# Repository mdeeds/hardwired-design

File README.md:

# Hardwired Design

This repository contains a curated collection of "vintage" electronic
schematics recreated in KiCad format, alongside original hardware designs
for the Hardwired Design project. It serves as a resource for circuit design,
PCB layouts, and 3D models.

## Project Overview

This project is an open resource that includes reference vintage circuitry
with the designs developed for the Hardwired Design project - a public
synthesizer design and manufacturing project. All schematics and layouts
are maintained using modern EDA tools to ensure they are accessible for
contemporary manufacturing and hobbyist use.

## Setup

To get started with these designs, follow the instructions below.

### 1. Install KiCad

This project is designed for **KiCad v10.0**. Please ensure you have the
correct version installed to avoid compatibility issues with the schema and
layout files.

*   Download: [KiCad Official Website](https://www.kicad.org/download/)

### 2. Clone the Repository

Clone this repository to your local machine using Git:

```bash
git clone https://github.com/mdeeds/hardwired-design.git
```

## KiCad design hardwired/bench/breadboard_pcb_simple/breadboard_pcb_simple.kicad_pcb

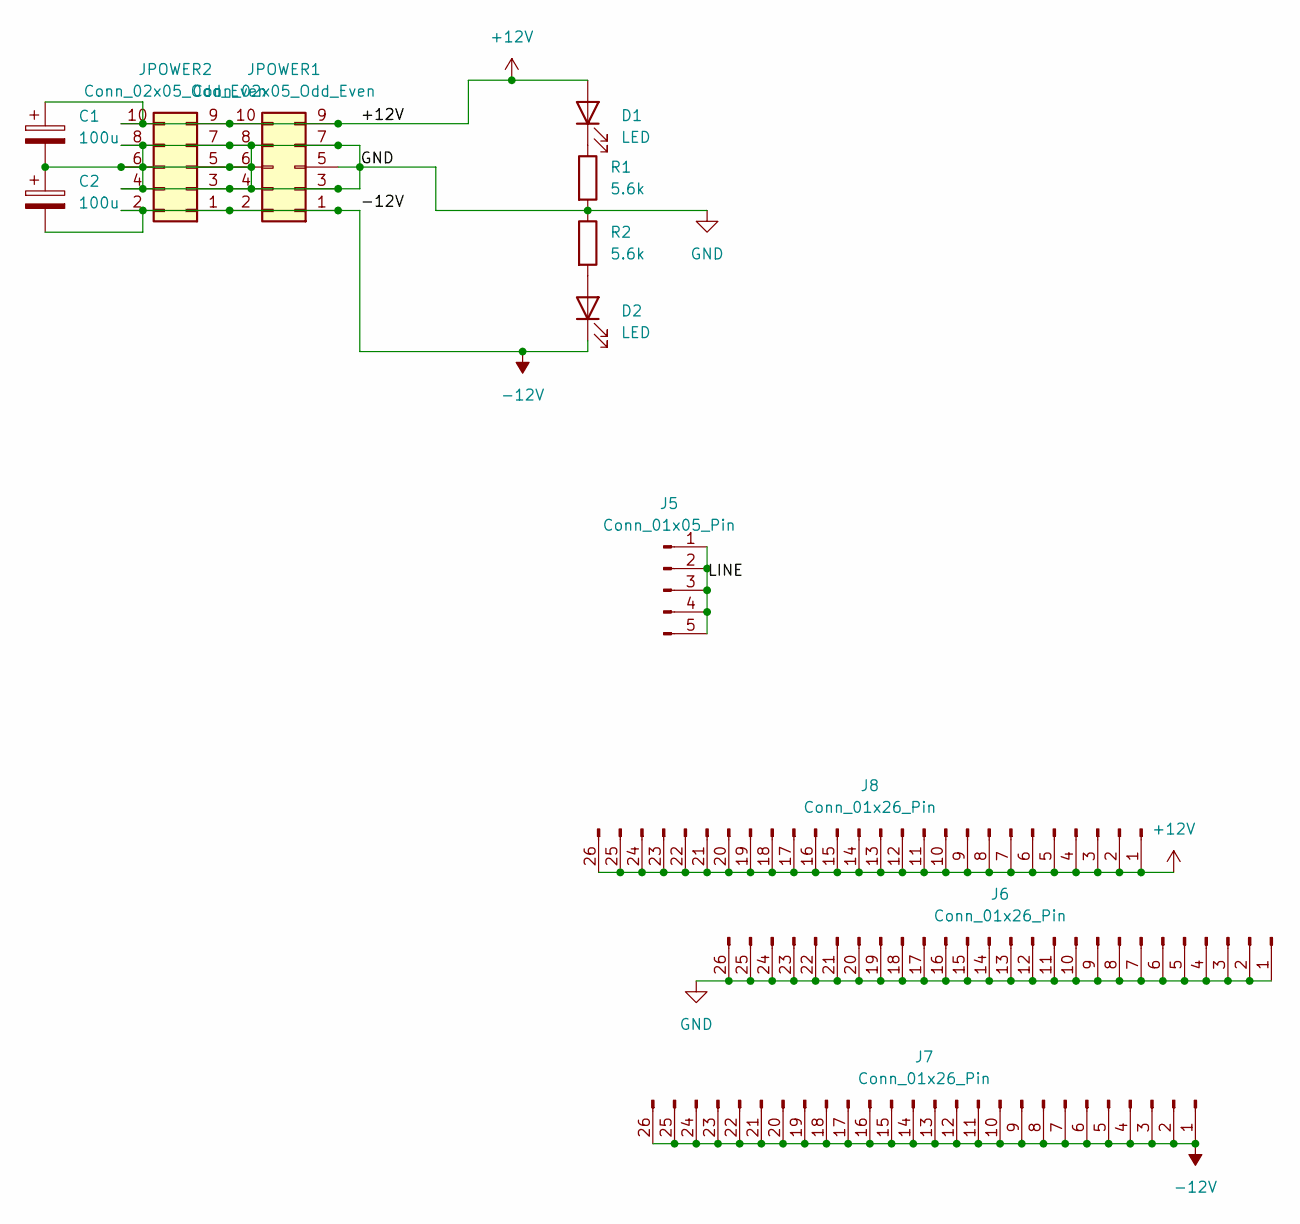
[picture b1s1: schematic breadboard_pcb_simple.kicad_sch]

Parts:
C1, C2: 100u; CP_Radial_D5.0mm_P2.00mm
D1, D2: LED; LED_D3.0mm_Clear
J5: Conn_01x05_Pin; PinHeader_1x05_P2.54mm_Vertical
J6, J7, J8: Conn_01x26_Pin; PinHeader_1x26_P2.54mm_Vertical
JPOWER1, JPOWER2: Conn_02x05_Odd_Even; Amphenol 71918-110LF 2.54 2x05 IDC
R1, R2: 5.6k; R_Axial_DIN0309_L9.0mm_D3.2mm_P2.54mm_Vertical

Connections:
+12V: C1.1, D1.2 (A), J8.1, J8.2, J8.3, J8.4, J8.5, J8.6, J8.7, J8.8, J8.9, J8.10, J8.11, J8.12, J8.13, J8.14, J8.15, J8.16, J8.17, J8.18, J8.19, J8.20, J8.21, J8.22, J8.23, J8.24, J8.25, J8.26, JPOWER1.9, JPOWER1.10, JPOWER2.9, JPOWER2.10
-12V: C2.2, D2.1 (K), J7.1, J7.2, J7.3, J7.4, J7.5, J7.6, J7.7, J7.8, J7.9, J7.10, J7.11, J7.12, J7.13, J7.14, J7.15, J7.16, J7.17, J7.18, J7.19, J7.20, J7.21, J7.22, J7.23, J7.24, J7.25, J7.26, JPOWER1.1, JPOWER1.2, JPOWER2.1, JPOWER2.2
GND: C1.2, C2.1, J6.1, J6.2, J6.3, J6.4, J6.5, J6.6, J6.7, J6.8, J6.9, J6.10, J6.11, J6.12, J6.13, J6.14, J6.15, J6.16, J6.17, J6.18, J6.19, J6.20, J6.21, J6.22, J6.23, J6.24, J6.25, J6.26, JPOWER1.3, JPOWER1.4, JPOWER1.5, JPOWER1.6, JPOWER1.7, JPOWER1.8, JPOWER2.3, JPOWER2.4, JPOWER2.5, JPOWER2.6, JPOWER2.7, JPOWER2.8, R1.2, R2.1
unnamed: D1.1 (K), R1.1
unnamed: D2.2 (A), R2.2
unnamed: J5.1, J5.2, J5.3, J5.4, J5.5

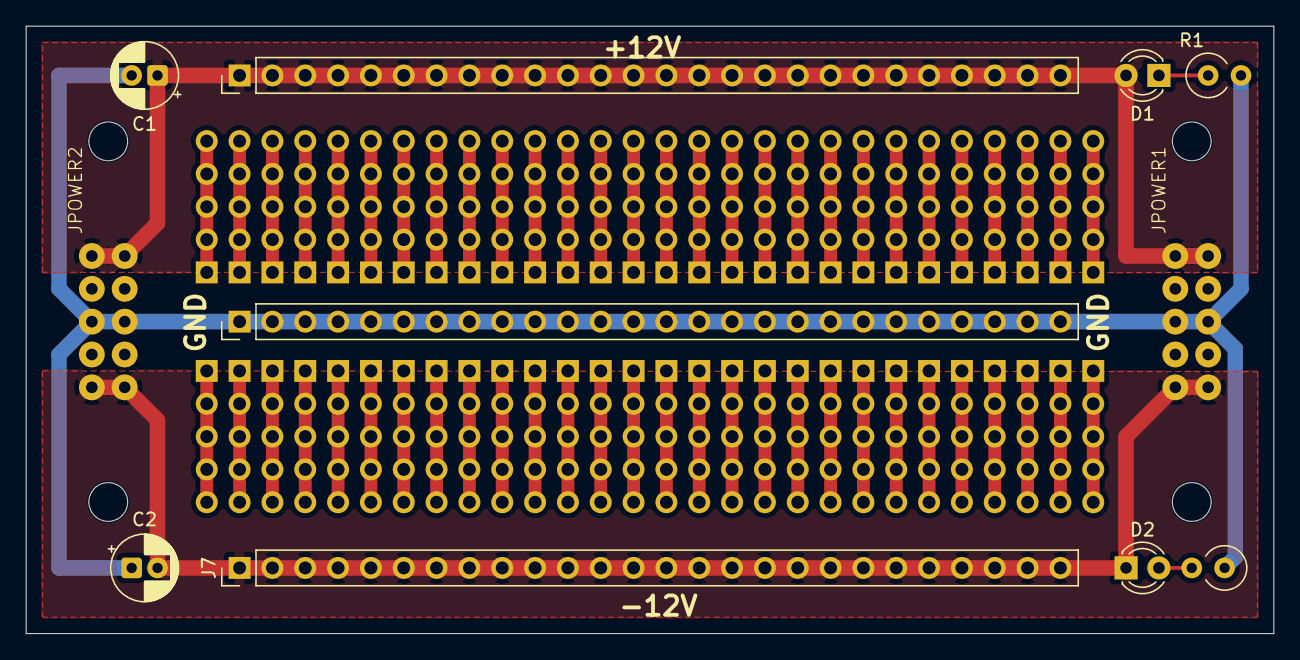
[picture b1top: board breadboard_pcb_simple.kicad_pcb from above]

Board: 2 copper layers, 96.5 x 47.0 mm, 11 parts (0 on the bottom side), 5 nets.

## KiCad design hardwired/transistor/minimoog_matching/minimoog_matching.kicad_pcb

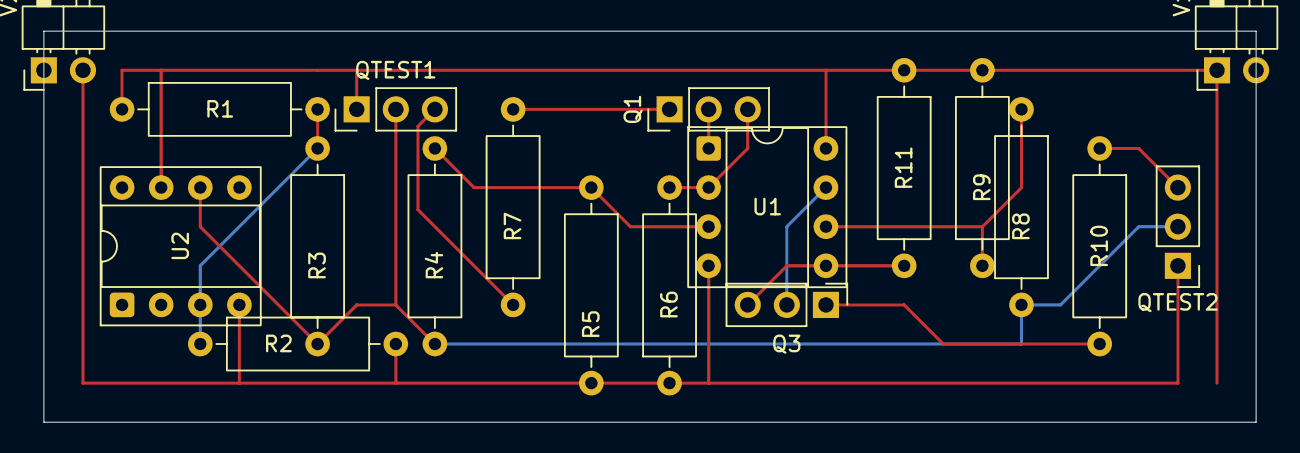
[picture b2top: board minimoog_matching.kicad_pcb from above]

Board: 2 copper layers, 78.7 x 25.4 mm, 19 parts (0 on the bottom side), 15 nets.

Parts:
Q1: NPN; PinHeader_1x03_P2.54mm_Vertical
Q3: PNP; PinHeader_1x03_P2.54mm_Vertical
QTEST1: NPN; PinHeader_1x03_P2.54mm_Vertical
QTEST2: PNP; PinHeader_1x03_P2.54mm_Vertical
R1, R2: 100k; R_Axial_DIN0309_L9.0mm_D3.2mm_P12.70mm_Horizontal
R3: 100; R_Axial_DIN0309_L9.0mm_D3.2mm_P12.70mm_Horizontal
R4, R5, R8, R9: 12k; R_Axial_DIN0309_L9.0mm_D3.2mm_P12.70mm_Horizontal
R6, R11: 47k; R_Axial_DIN0309_L9.0mm_D3.2mm_P12.70mm_Horizontal
R7, R10: 10k; R_Axial_DIN0309_L9.0mm_D3.2mm_P12.70mm_Horizontal
U1: Opamp_Dual; DIP-8_W7.62mm_Socket
U2: BUF634P; DIP-8_W7.62mm_Socket
V1, V2: 10; PinHeader_1x02_P2.54mm_Horizontal

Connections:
0: R1.2, R2.1, R3.1, U2.3 (V_{IN})
+10V: QTEST1.1 (C), R1.1, R9.2, R11.1, U1.8 (V+), U2.7 (V+), V1.1
-10V: QTEST2.1 (C), R2.2, R5.2, R6.1, U1.4 (V-), U2.4 (V-), V2.2
GND: QTEST1.2 (B), QTEST2.2 (B), R3.2, R4.2, R8.2, U2.6
unnamed: Q1.2 (B), U1.1
unnamed: Q1.1 (C), R7.2
unnamed: Q1.3 (E), R6.2, U1.2 (-)
unnamed: Q3.2 (B), U1.7
unnamed: Q3.1 (C), R10.2
unnamed: Q3.3 (E), R11.2, U1.5 (+)
unnamed: QTEST1.3 (E), R7.1
unnamed: QTEST2.3 (E), R10.1
unnamed: R4.1, R5.1, U1.3 (+)
unnamed: R8.1, R9.1, U1.6 (-)
unnamed: V1.2, V2.1

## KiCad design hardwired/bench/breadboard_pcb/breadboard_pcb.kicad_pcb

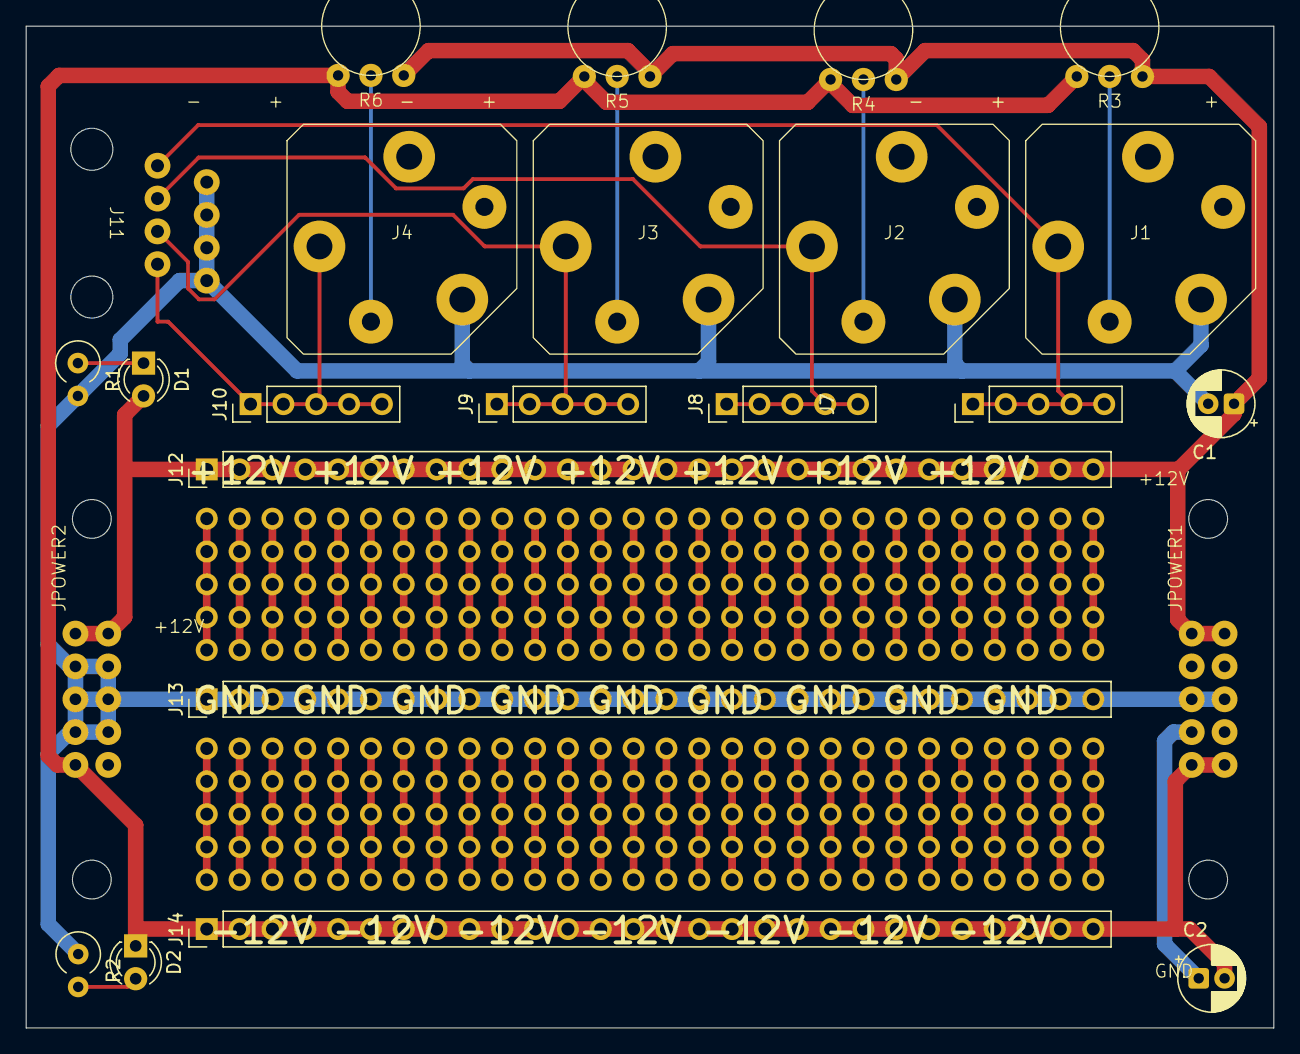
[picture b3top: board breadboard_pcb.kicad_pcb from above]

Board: 2 copper layers, 96.5 x 77.5 mm, 24 parts (0 on the bottom side), 13 nets.

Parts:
C1, C2: 100u; CP_Radial_D5.0mm_P2.00mm
D1, D2: LED; LED_D3.0mm_Clear
J1: CV1; ACJM-MV3-2S 3.5mm Audio Jack Mono Switched
J2: CV2; ACJM-MV3-2S 3.5mm Audio Jack Mono Switched
J3: CV3; ACJM-MV3-2S 3.5mm Audio Jack Mono Switched
J4: CV4; ACJM-MV3-2S 3.5mm Audio Jack Mono Switched
J7, J8, J9, J10: Conn_01x05_Pin; PinHeader_1x05_P2.54mm_Vertical
J11: RJ45; Keystone RJ45 949
J12, J13, J14: Conn_01x28_Pin; PinHeader_1x28_P2.54mm_Vertical
JPOWER1, JPOWER2: Conn_02x05_Odd_Even; Amphenol 71918-110LF 2.54 2x05 IDC
R1, R2: 330; R_Axial_DIN0309_L9.0mm_D3.2mm_P2.54mm_Vertical
R3, R4, R5, R6: Potentiometer; BOURNS 2.54 335T POTENTIOMETER

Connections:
+12V: C1.1, D1.2 (A), J12.1, J12.2, J12.3, J12.4, J12.5, J12.6, J12.7, J12.8, J12.9, J12.10, J12.11, J12.12, J12.13, J12.14, J12.15, J12.16, J12.17, J12.18, J12.19, J12.20, J12.21, J12.22, J12.23, J12.24, J12.25, J12.26, J12.27, J12.28, JPOWER1.9, JPOWER1.10, JPOWER2.9, JPOWER2.10, R3.3, R4.3, R5.3, R6.3
-12V: C2.2, D2.1 (K), J14.1, J14.2, J14.3, J14.4, J14.5, J14.6, J14.7, J14.8, J14.9, J14.10, J14.11, J14.12, J14.13, J14.14, J14.15, J14.16, J14.17, J14.18, J14.19, J14.20, J14.21, J14.22, J14.23, J14.24, J14.25, J14.26, J14.27, J14.28, JPOWER1.1, JPOWER1.2, JPOWER2.1, JPOWER2.2, R3.1, R4.1, R5.1, R6.1
/J1_T: J1.T, J7.1, J7.2, J7.3, J7.4, J7.5, J11.1
/J1_TN: J1.TN, R3.2
/J2_T: J2.T, J8.1, J8.2, J8.3, J8.4, J8.5, J11.3
/J2_TN: J2.TN, R4.2
/J3_T: J3.T, J9.1, J9.2, J9.3, J9.4, J9.5, J11.5
/J3_TN: J3.TN, R5.2
/J4_T: J4.T, J10.1, J10.2, J10.3, J10.4, J10.5, J11.7
/J4_TN: J4.TN, R6.2
GND: C1.2, C2.1, J1.S, J2.S, J3.S, J4.S, J11.2, J11.4, J11.6, J11.8, J13.1, J13.2, J13.3, J13.4, J13.5, J13.6, J13.7, J13.8, J13.9, J13.10, J13.11, J13.12, J13.13, J13.14, J13.15, J13.16, J13.17, J13.18, J13.19, J13.20, J13.21, J13.22, J13.23, J13.24, J13.25, J13.26, J13.27, J13.28, JPOWER1.3, JPOWER1.4, JPOWER1.5, JPOWER1.6, JPOWER1.7, JPOWER1.8, JPOWER2.3, JPOWER2.4, JPOWER2.5, JPOWER2.6, JPOWER2.7, JPOWER2.8, R1.2, R2.1
unnamed: D1.1 (K), R1.1
unnamed: D2.2 (A), R2.2

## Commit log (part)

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2026-04-05 Add Kicad .gitignore
2026-04-05 Add schematics for the ARP AXXE LFO
2026-04-05 LFO updates and simulation
2026-04-05 Add keyboard voltage sampling circuit
2026-04-05 Ignore history
2026-04-05 Add oneshot design skill and test it out with a sample and hold circuit
2026-04-05 Add a Gemini-Designed oscillator
2026-04-06 Add "audit" skill
2026-04-06 Introduce non-functional Gemini designed oscillator circuit
2026-04-06 Simulation for oscillator
2026-04-06 Improve gitignore
2026-04-06 Small improvements to oscillator design file.
2026-04-06 Update Audit skill
2026-04-06 Auditted design
2026-04-07 Add nested, resumable skills.
2026-04-07 Sawtooth from Gemini
2026-04-07 Arp AXXE VCF Trace
2026-04-07 Add exponentiator
2026-04-07 Exponential Current Converter and spice runner
2026-04-08 updated oneshot skill to include simulation and itteration.
2026-04-08 new exponetial converter.
2026-04-08 robustness and save data as csv
2026-04-08 increased voltage output to make it eaiser to measure. added tuning and trouble shooting notes.
2026-04-10 Improve some list formatting
2026-04-10 Introduce transistor evaluation project
2026-04-10 Transistor matching procedure
2026-04-10 added support for .cir files
2026-04-10 worst case analysis
2026-04-10 minor design tweaks.
2026-04-10 Creates an HTML file to help with debuging a circuit based on the .md, .cir, or .csv
2026-04-10 skills matched to Eurorack +/-12v (my bad, I had +/-15v at one point)
2026-04-10 improve library handling.
2026-04-10 added kit transistors
2026-04-10 added Vetco SPICE library
2026-04-19 Add a simple SVG to match my breadboard
2026-04-21 Add minimoog circuit
2026-04-21 standardize case of nets
2026-04-23 Ignore PCB layouts
2026-04-23 Add DI circuit
2026-04-23 Add some layout for DI box
2026-04-23 minimoog mathcing updates
2026-04-23 Audio Interface oscilloscope
2026-05-02 A whole bunch of circuits
2026-05-05 clean up of html and added NE5532
2026-05-05 table cleanup
2026-05-05 script to digitize charts from datasheets
2026-05-05 script to itterativly adjust a model to match data sheet or measurement data
2026-05-05 dll path more robust.
2026-05-05 added current curves
2026-05-05 ignore py cache
2026-05-09 Many Kicad drawings
2026-05-19 renamed agent to agents to match gemini and copilot standard.
2026-05-20 feat: Add simple transistor sawtooth oscillator subsystem and interactive simulation dashboard
2026-05-21 Massive dump of circuits and code
2026-05-21 Delete .history
    Delete me
2026-05-23 Add breadboard app and corresponding test circuit
2026-05-23 Kicad version of simple transitor saw circuit
2026-05-23 Add breadboard PCB
2026-05-23 Simpler bb pcb
2026-05-23 Simpler version of the BB
2026-05-28 Add improved breadboard PCB
2026-06-13 Improve oscilloscope
2026-06-13 DI (Signal Tracer) circuit improvements
2026-06-17 Add new Volt Per Octave circuit. Thank you Copilot!
2026-06-20 buffer comparison scripts
2026-06-20 updated LM358N based on bench measurments to correctly model current limit.
